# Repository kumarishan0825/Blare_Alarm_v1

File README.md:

# Blare_Alarm_v1 - ESP32-C3 Hardware Project

Welcome to the complete repository for the Blare Alarm project. This project a fully custom hardware layout driven by an ESP32-C3 microcontroller, custom enclosure CAD models, and production-ready manufacturing files.

---

## Project Showcase

### Overall Clock Design

### Circuit Schematic

### PCB Board Layout

### Enclosure & Integration Fit

---

## Bill of Materials (BOM)

| Component Description | Quantity | Package /Type | Notes |
| :--- | :--- | :--- | :--- |
| ESP32-C3 Microcontroller | 1 | Custom Footprint | Main system processor |
| Mechanical Keyboard Switches | 4 | 2-Pin Through-Hole (PTH) | Input keys for interface |
| Matching Keycaps | 4 | Plastic Caps | Fitted onto mechanical switches |
| 3.3V Buzzer | 1 | Through-Hole (PTH) | Mounted on PCB for alarm audio |
| 2.25in TFT Display | 1 | Screen Module | Main clock screen interface |
| Custom Enclosure Case | 1 | 3D Printed (STEP Model) | Physical shell designed in Onshape |

## Repository Organization
1)CAD/: Core 3D design models.
2)Firmware/: Arduino application source code.
3)PCB/: Portable KiCad source designs with project related footprint libraries.
4)Production/: Factory-ready "gerbers.zip" manufacturing archive.

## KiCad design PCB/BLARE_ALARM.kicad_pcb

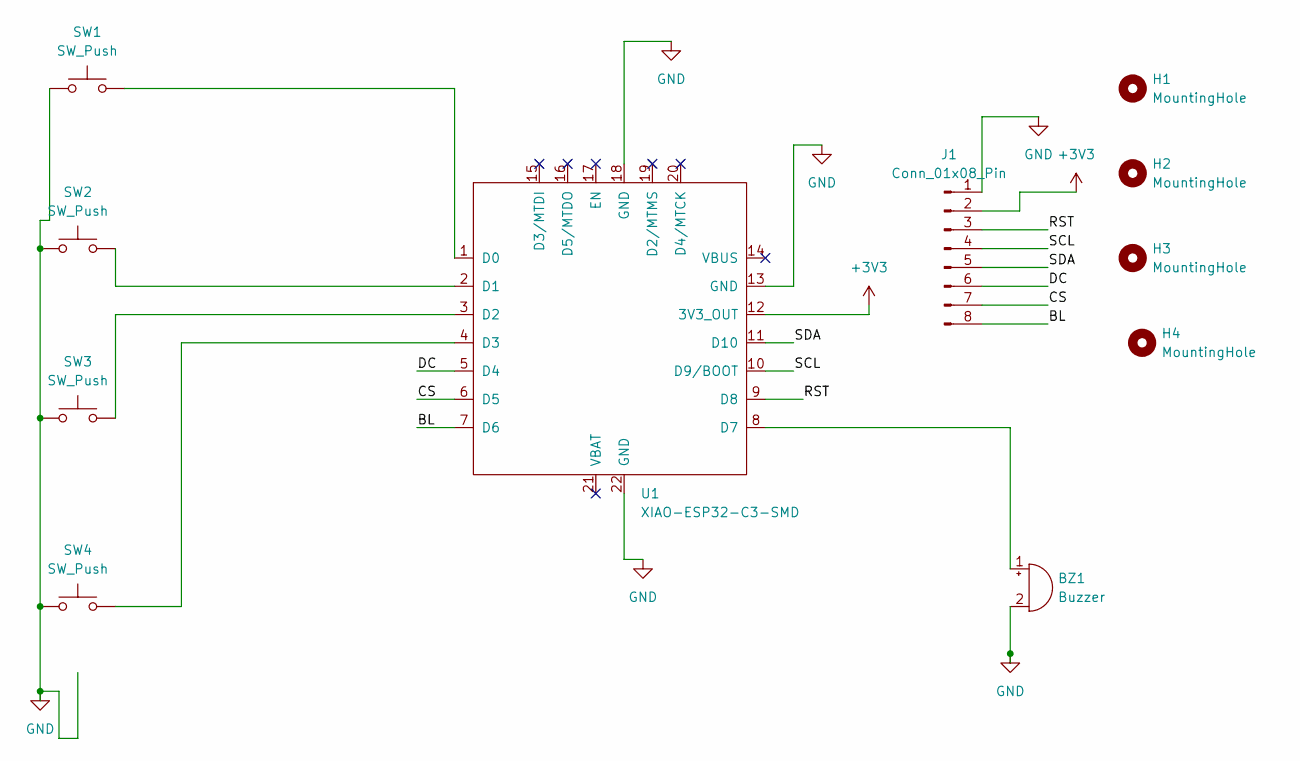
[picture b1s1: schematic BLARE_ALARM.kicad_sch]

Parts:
BZ1: Buzzer; Buzzer_12x9.5RM7.6
H1, H2, H3, H4: MountingHole; MountingHole_3.2mm_M3
J1: Conn_01x08_Pin; PinSocket_1x08_P2.54mm_Vertical
SW1, SW2, SW3, SW4: SW_Push; SW_Cherry_MX_1.00u_PCB
U1: XIAO-ESP32-C3-SMD

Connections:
+3V3: J1.2, U1.12 (3V3_OUT)
/BL: J1.8, U1.7 (D6)
/CS: J1.7, U1.6 (D5)
/DC: J1.6, U1.5 (D4)
/RST: J1.3, U1.9 (D8)
/SCL: J1.4, U1.10 (D9/BOOT)
/SDA: J1.5, U1.11 (D10)
GND: BZ1.2 (-), J1.1, SW1.1, SW2.1, SW3.1, SW4.1, U1.13 (GND), U1.18 (GND), U1.22 (GND)
unnamed: BZ1.1 (+), U1.8 (D7)
unnamed: SW1.2, U1.1 (D0)
unnamed: SW2.2, U1.2 (D1)
unnamed: SW3.2, U1.3 (D2)
unnamed: SW4.2, U1.4 (D3)

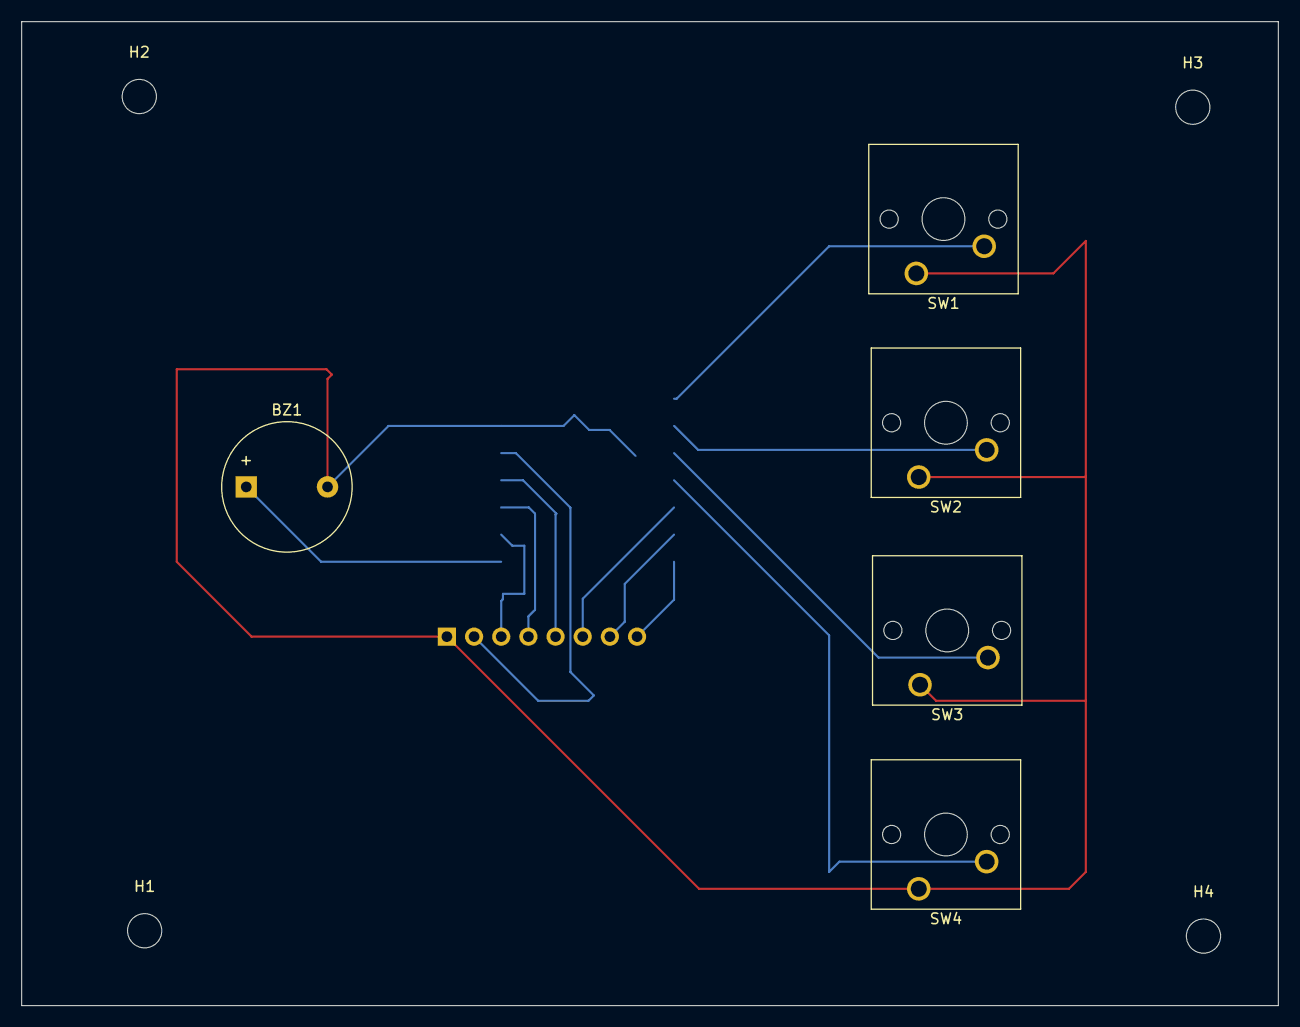
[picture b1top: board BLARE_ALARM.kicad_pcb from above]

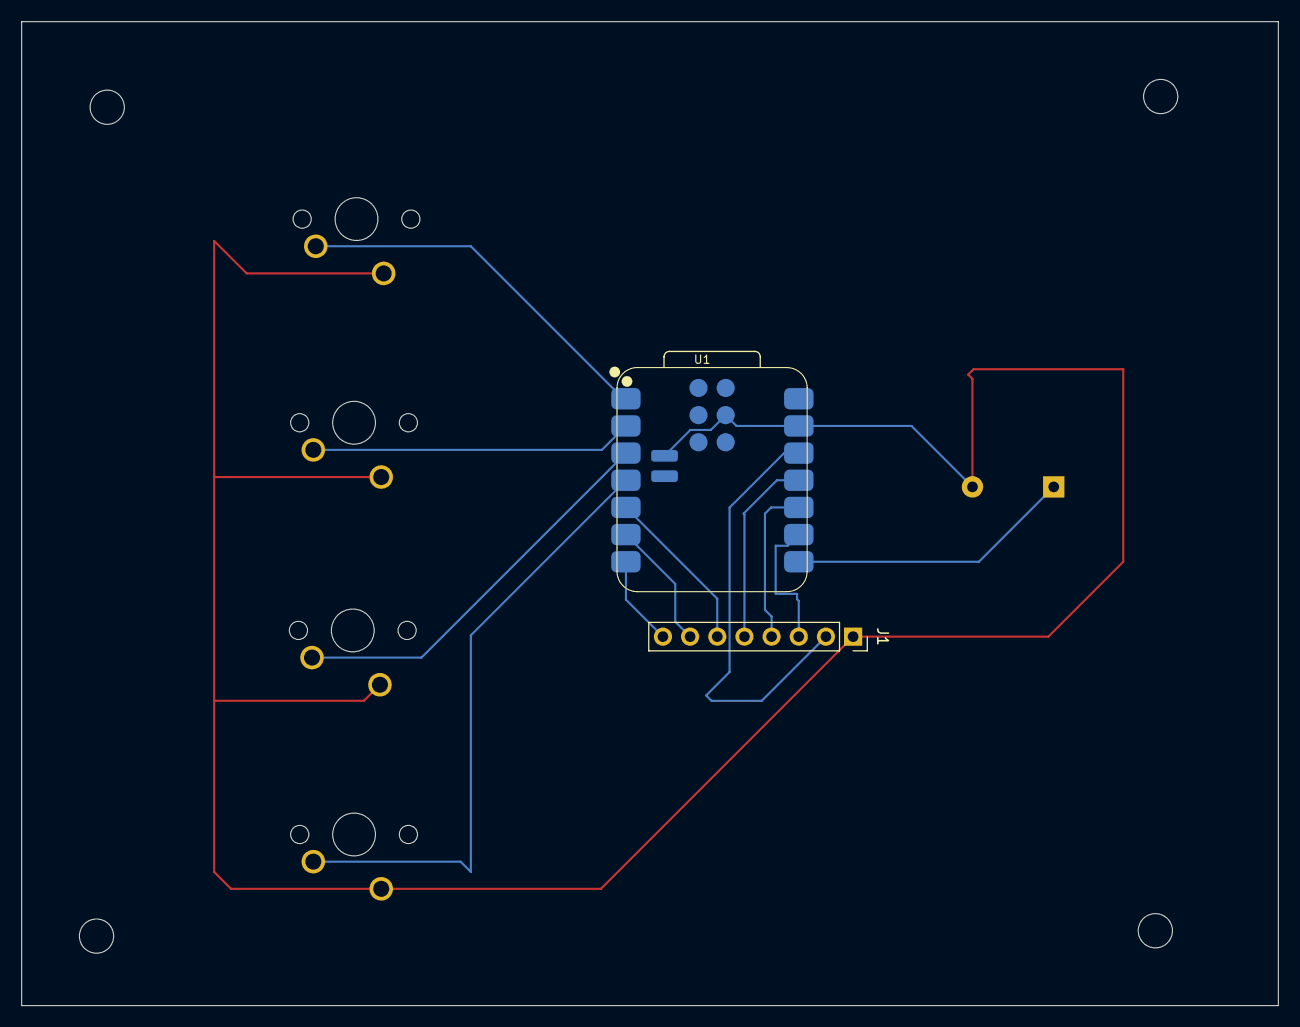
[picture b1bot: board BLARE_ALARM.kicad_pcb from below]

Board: 2 copper layers, 117.5 x 92.0 mm, 11 parts (2 on the bottom side), 13 nets.
